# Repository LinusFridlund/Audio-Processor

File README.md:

# Audio-Processor

A modular Raspberry Pi based audio processor with custom designed hardware

## Overview
This audio Processor is a home-stereo DSP unit built around a Raspberry Pi 5. The Pi handles input selection, digital signal processing and the touchscreen UI, while all audio input and output happens on custom PCBs designed from scratch in KiCad.

The hardware is modular, every audio module shares the same 60 × 100 mm, 4-layer form factor and a common 20-pin connector carrying I²S audio, I²C control and power. Modules can be added or swapped without redesigning the rest of the system.

## Hardware

### DAC module
A two-channel, balanced-output DAC using the ESS ES9039Q2M chip. High quality components have been chosen for the best possible performance, including the OPA1612 opamps in the output stages and the ultra low noise power regulators used.

### Digital input module
Receives digital audio from two S/PDIF and tvo coaxial inputs and sends it over I²S to the Raspberry Pi. It is built around the TI SRC4392 IC which handles input multiplexing and sample rate conversion to sync the outgoing data to the Raspberry Pis I²S clock.

### Power Supply
The power supply converts 230V AC from the wall into voltages used by the rest of the system. These include +5V for the Raspberry Pi, and +-15V for the analog boards.

## Software
The software has two main functions, to run a custom GUI made using Kivy in Python, and running the DSP backend. 

## Repository Structure
```
Audio-Processor/
├── Hardware/
│   ├── Digital Input Module/   KiCad project + production files
│   └── DAC Module/             KiCad project, Gerbers, bring-up notes
├── Software/
│   ├── gui/                    Kivy touchscreen interface
│   └── audio_engine/           DSP and hardware control (in progress)
├── docs/                       Diagrams and images
└── LICENSE
```

## Future expansion

## Project Status / Roadmap
Currently the two DAC boards are assembled and initial testing looks promising. An early version of a GUI is up and running on the Raspberry Pi.
My current focus is finishing up the power supply and digital input modules and hopefully getting them ordered soon.

## License
Released under the MIT License.

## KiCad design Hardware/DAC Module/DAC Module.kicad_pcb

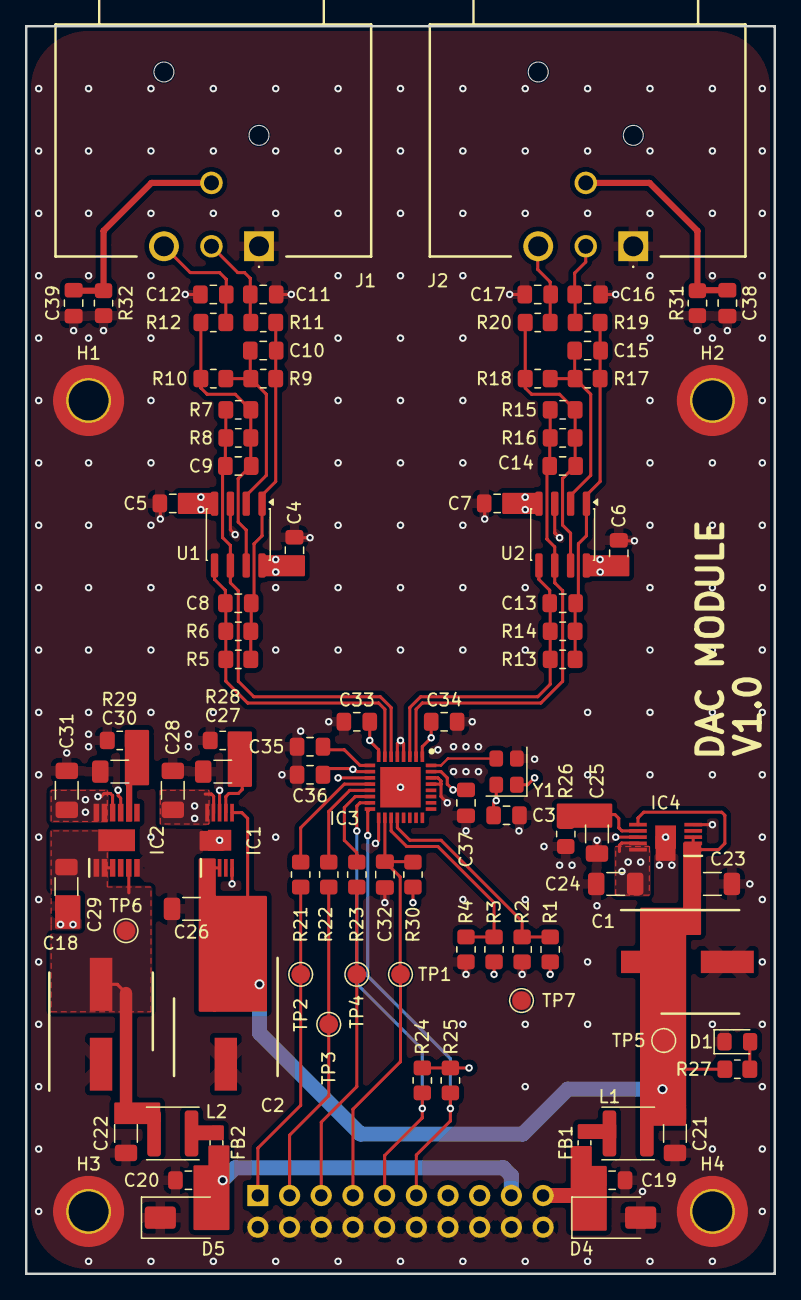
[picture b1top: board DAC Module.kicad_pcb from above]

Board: 4 copper layers, 60.0 x 100.0 mm, 99 parts (1 on the bottom side), 43 nets.

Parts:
C1, C2, C18: 47u; CAPAE830X650N
C3, C19, C20, C32: 100n; C_0805_2012Metric_Pad1.18x1.45mm_HandSolder
C4, C5, C6, C7: 0.47u; C_0805_2012Metric_Pad1.18x1.45mm_HandSolder
C8, C9, C13, C14: 510p (C0G/NP0); C_0805_2012Metric_Pad1.18x1.45mm_HandSolder
C10, C15: 10p (C0G/NP0); C_0805_2012Metric_Pad1.18x1.45mm_HandSolder
C11, C12, C16, C17: 2.2n (C0G/NP0); C_0805_2012Metric_Pad1.18x1.45mm_HandSolder
C21, C22, C24, C28, C31: 10u; C_1206_3216Metric_Pad1.33x1.80mm_HandSolder
C23, C26, C29: 4.7u; C_1206_3216Metric_Pad1.33x1.80mm_HandSolder
C25, C27, C30: 0.47u; C_1206_3216Metric_Pad1.33x1.80mm_HandSolder
C33, C34, C35, C36, C37: 1u; C_0805_2012Metric_Pad1.18x1.45mm_HandSolder
C38, C39: 0.1u; C_0805_2012Metric_Pad1.18x1.45mm_HandSolder
D1: LED; LED_0805_2012Metric_Pad1.15x1.40mm_HandSolder
D4, D5: SMAJ16A; D_SMA
FB1, FB2: BLM18SP601SN1D; L_0603_1608Metric_Pad1.05x0.95mm_HandSolder
H1, H2, H3, H4: M3 hole; MountingHole_3.2mm_M3_ISO7380_Pad_TopBottom
IC1, IC4: LT3042IMSE#PBF; SOP50P490X110-11N
IC2: LT3094IMSE#PBF; SOP65P490X110-13N
IC3: ES9039Q2M; QFN50P500X500X90-33N-D
J1, J2: NC3MAH
J6: Conn_02x10_Odd_Even; PinHeader_2x10_P2.54mm_Vertical
L1, L2: 22uH; L_APV_ANR4026
R1, R2, R3, R4: 0; R_0805_2012Metric_Pad1.20x1.40mm_HandSolder
R5, R6, R7, R8, R13, R14, R15, R16: 3k6 (THIN FILM); R_0805_2012Metric_Pad1.20x1.40mm_HandSolder
R9, R10, R17, R18: 4k7 (THIN FILM); R_0805_2012Metric_Pad1.20x1.40mm_HandSolder
R11, R12, R19, R20: 140 (THIN FILM); R_0805_2012Metric_Pad1.20x1.40mm_HandSolder
R21, R22, R23: 50; R_0805_2012Metric_Pad1.20x1.40mm_HandSolder
R24, R25: 4.7k; R_0805_2012Metric_Pad1.20x1.40mm_HandSolder
R26: 33.2k 1%; R_0805_2012Metric_Pad1.20x1.40mm_HandSolder
R27: 6.8k; R_0805_2012Metric_Pad1.20x1.40mm_HandSolder
R28, R29: 121k 1%; R_0805_2012Metric_Pad1.20x1.40mm_HandSolder
R30: 47k; R_0805_2012Metric_Pad1.20x1.40mm_HandSolder
R31, R32: 10k; R_0805_2012Metric_Pad1.20x1.40mm_HandSolder
TP1, TP2, TP3, TP4, TP5, TP6, TP7: TestPoint_Small; TestPoint_Pad_D1.5mm
U1, U2: OPA1612AxD; SOIC-8_3.9x4.9mm_P1.27mm
Y1: NSC5083D; Oscillator_SMD_Abracon_ASE-4Pin_3.2x2.5mm

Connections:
+3V3: C3.1, C24.1, C33.1, C34.1, C36.1, C37.1, IC3.1 (AVCC_DAC1), IC3.8 (AVCC_DAC2), IC3.10 (AVDD), IC3.31 (VCCA), IC4.9 (OUTS), IC4.10 (OUT), R1.1, R3.1, R24.2, R25.2, R30.2, Y1.1 (EN), Y1.4 (Vdd)
+12V: C4.1, C6.1, C28.1, IC1.9 (OUTS), IC1.10 (OUT), U1.8 (V+), U2.8 (V+)
+15V: C1.1 (+), C2.1 (+), C21.1, C23.1, C26.1, IC1.1 (IN_1), IC1.2 (IN_2), IC1.3 (EN/UV), IC1.6 (PGFB), IC4.1 (IN_1), IC4.2 (IN_2), IC4.3 (EN/UV), IC4.6 (PGFB), L1.2, R27.2, TP5.1 (1_1)
+15V_IN: C19.1, D4.1 (A1), FB1.1, J6.19
-12V: C5.2, C7.2, C31.1, IC2.10 (OUTS), IC2.11 (OUT_1), IC2.12 (OUT_2), U1.4 (V-), U2.4 (V-)
-15V: C18.2 (-), C22.2, C29.1, IC2.1 (IN_1), IC2.2 (IN_2), IC2.3 (EN/UV), IC2.5 (PGFB), IC2.13 (IN_3), L2.2, TP6.1 (1_1)
-15V_IN: C20.2, D5.2 (A2), FB2.1, J6.17
/DAC Module/DVDD: C35.1, IC3.9 (DVDD)
/DAC Module/MCLK: IC3.32 (MCLK), Y1.3 (OUT)
/Power supply/SET_3V3: C25.1, IC4.7 (SET), R26.2
/Power supply/SET_12V: C27.1, IC1.7 (SET), R28.2
/Power supply/SET_-12V: C30.1, IC2.8 (SET), R29.2
ADDR0: IC3.20 (MISO/ADDR0/MUTE_CTRL), R1.2, R2.1
ADDR1: IC3.19 (SS/ADDR1/HW2), R3.2, R4.1
DAC1: C13.1, IC3.3 (DAC1), R13.1, R14.1, U2.5 (+)
DAC1_B: C14.1, IC3.2 (DAC1B), R15.1, R16.1, U2.6 (-)
DAC2: C8.1, IC3.7 (DAC2), R5.1, R6.1, U1.5 (+)
DAC2_B: C9.1, IC3.6 (DAC2B), R7.1, R8.1, U1.6 (-)
DAC_EN: C32.1, IC3.18 (CHIP_EN), J6.7, R30.1, TP1.1 (1_1)
GND: C1.2 (-), C2.2 (-), C3.2, C4.2, C5.1, C6.2, C7.1, C11.1, C12.1, C16.1, C17.1, C18.1 (+), C19.2, C20.1, C21.2, C22.1, C23.2, C24.2, C25.2, C26.2, C27.2, C28.2, C29.2, C30.2, C31.2, C32.2, C33.2, C34.2, C35.2, C36.2, C37.2, C38.1, C39.1, D1.1 (K), D4.2 (A2), D5.1 (A1), H1.1 (1_1), H2.1 (1_1), H3.1 (1_1), H4.1 (1_1), IC1.5 (ILIM), IC1.8 (GND_1), IC1.11 (GND_2), IC2.6 (I_LIM), IC2.9 (GND), IC3.4 (AGND_DAC1), IC3.5 (AGND_DAC2), IC3.11 (GND_1), IC3.17 (RT1), IC3.29 (MODE), IC3.30 (GND_2), IC3.33 (GND_3), IC4.5 (ILIM), IC4.8 (GND_1), IC4.11 (GND_2), J1.1, J2.1, J6.2, J6.4, J6.6, J6.8, J6.10, J6.12, J6.14, J6.16, J6.18, J6.20, R2.2, R4.2, R26.1, R28.1, R29.1, R31.1, R32.1, TP7.1 (1_1), U1.3 (+), U2.3 (+), Y1.2 (GND)
I2C_SCL: IC3.15 (SCLK/SCL/HW1), J6.9, R24.1
I2C_SDA: IC3.16 (MOSI/SDA/HW0), J6.11, R25.1
I2S_BCLK: J6.1, R21.1, TP2.1 (1_1)
I2S_DATA: J6.5, R23.1, TP4.1 (1_1)
I2S_WCLK: J6.3, R22.1, TP3.1 (1_1)
unnamed: C9.2, R7.2, R8.2, R10.2, R12.1, U1.7
unnamed: C8.2, C10.2, R5.2, R6.2, R9.1, R11.1, U1.1
unnamed: C11.2, J1.3, R11.2
unnamed: C12.2, J1.2, R12.2
unnamed: C13.2, C15.2, R13.2, R14.2, R17.1, R19.1, U2.1
unnamed: C14.2, R15.2, R16.2, R18.2, R20.1, U2.7
unnamed: C16.2, J2.3, R19.2
unnamed: C17.2, J2.2, R20.2
unnamed: C38.2, J2.G1, R31.2
unnamed: C39.2, J1.G1, R32.2
unnamed: D1.2 (A), R27.1
unnamed: FB1.2, L1.1
unnamed: FB2.2, L2.1
unnamed: IC3.13 (DATA1), R22.2
unnamed: IC3.14 (DATA2), R23.2
unnamed: IC3.12 (DATA_CLK), R21.2
unnamed: C10.1, R9.2, R10.1, U1.2 (-)
unnamed: C15.1, R17.2, R18.1, U2.2 (-)

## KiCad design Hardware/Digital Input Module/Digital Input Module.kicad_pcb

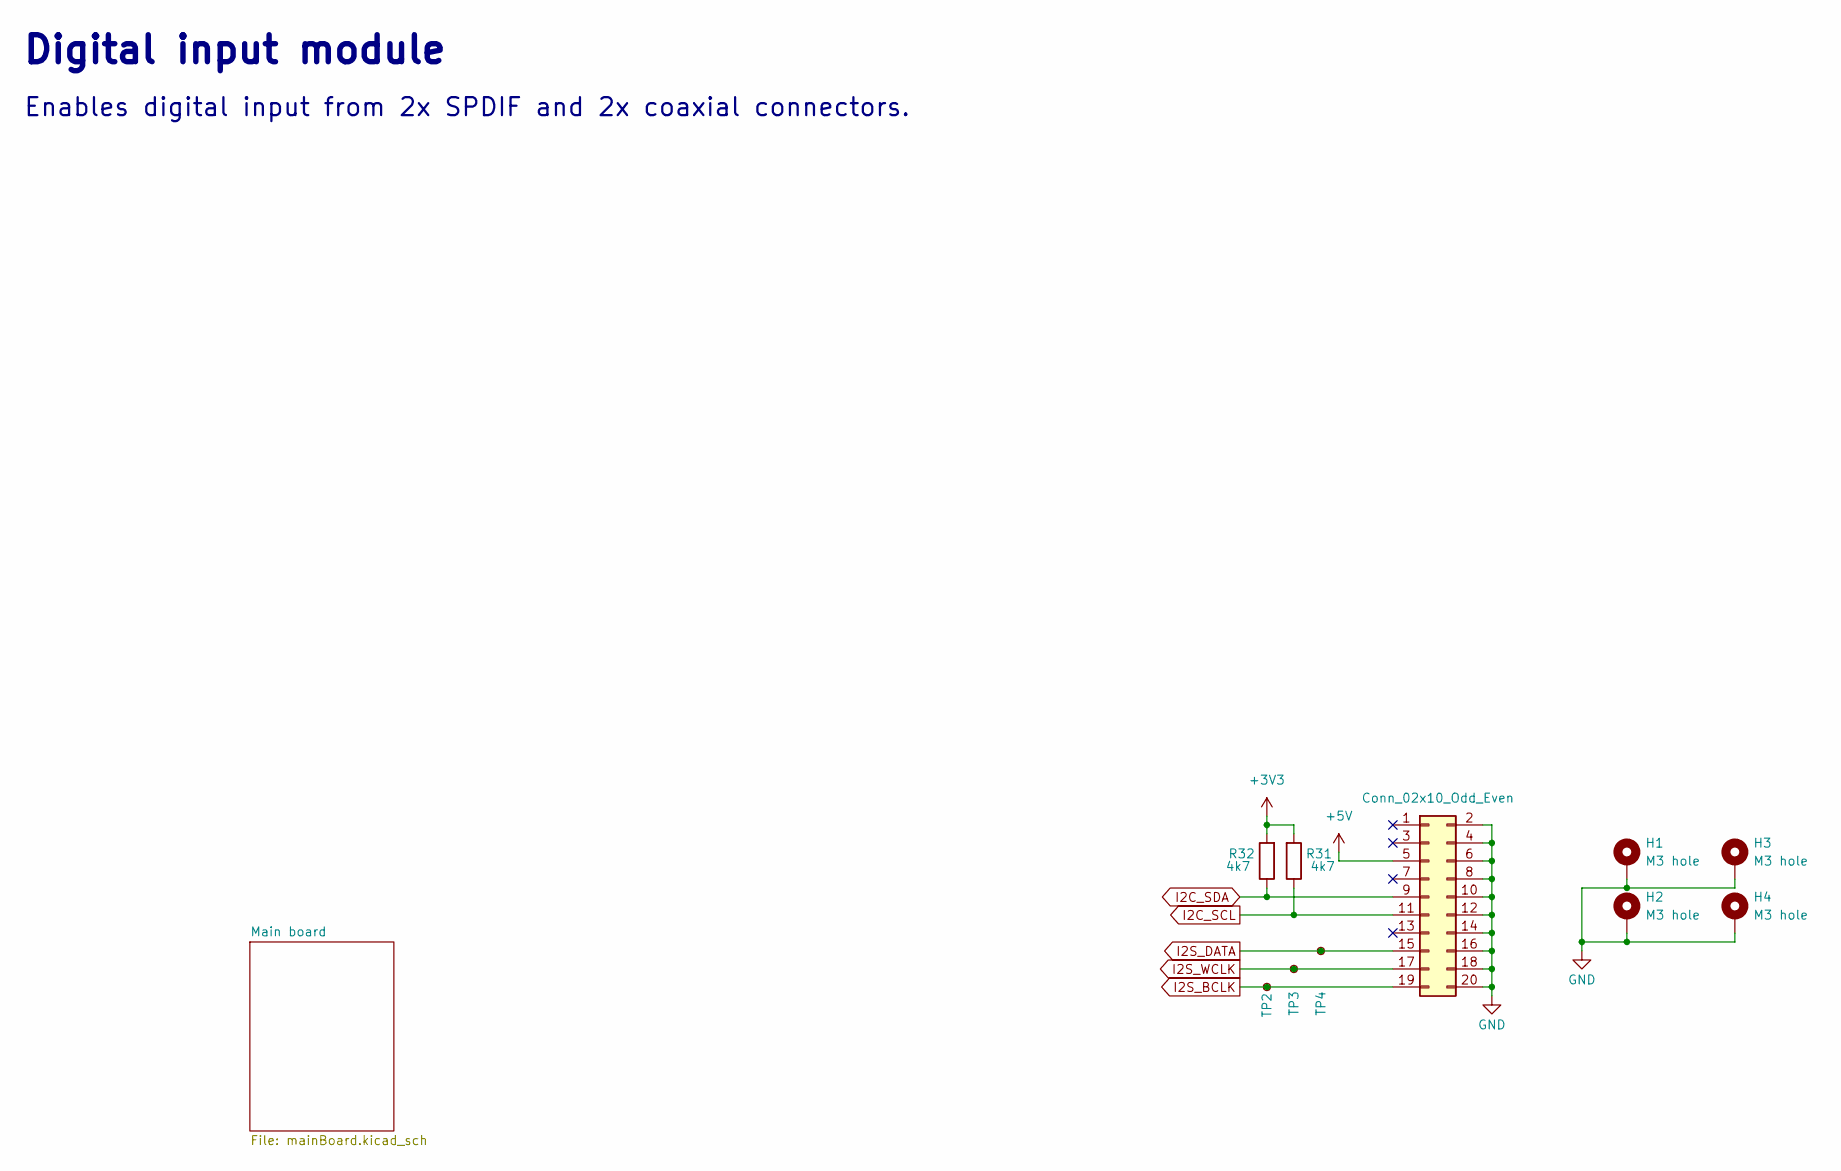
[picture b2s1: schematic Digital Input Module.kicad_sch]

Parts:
H1, H2, H3, H4: M3 hole; MountingHole_3.2mm_M3_ISO7380_Pad_TopBottom
J2: Conn_02x10_Odd_Even; PinHeader_2x10_P2.54mm_Vertical
R31, R32: 4k7; R_0805_2012Metric_Pad1.20x1.40mm_HandSolder
TP2, TP3, TP4: TestPoint_Small; TestPoint_Pad_D1.5mm

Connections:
+3V3: R31.2, R32.2; also elsewhere on the board
+5V: J2.5; also elsewhere on the board
GND: H1.1 (1_1), H2.1 (1_1), H3.1 (1_1), H4.1 (1_1), J2.2, J2.4, J2.6, J2.8, J2.10, J2.12, J2.14, J2.16, J2.18, J2.20; also elsewhere on the board
I2C_SCL: J2.11, R31.1; also elsewhere on the board
I2C_SDA: J2.9, R32.1; also elsewhere on the board
I2S_BCLK: J2.19, TP2.1; also elsewhere on the board
I2S_DATA: J2.15, TP4.1; also elsewhere on the board
I2S_WCLK: J2.17, TP3.1; also elsewhere on the board

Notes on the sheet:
Digital input module
Enables digital input from 2x SPDIF and 2x coaxial connectors.

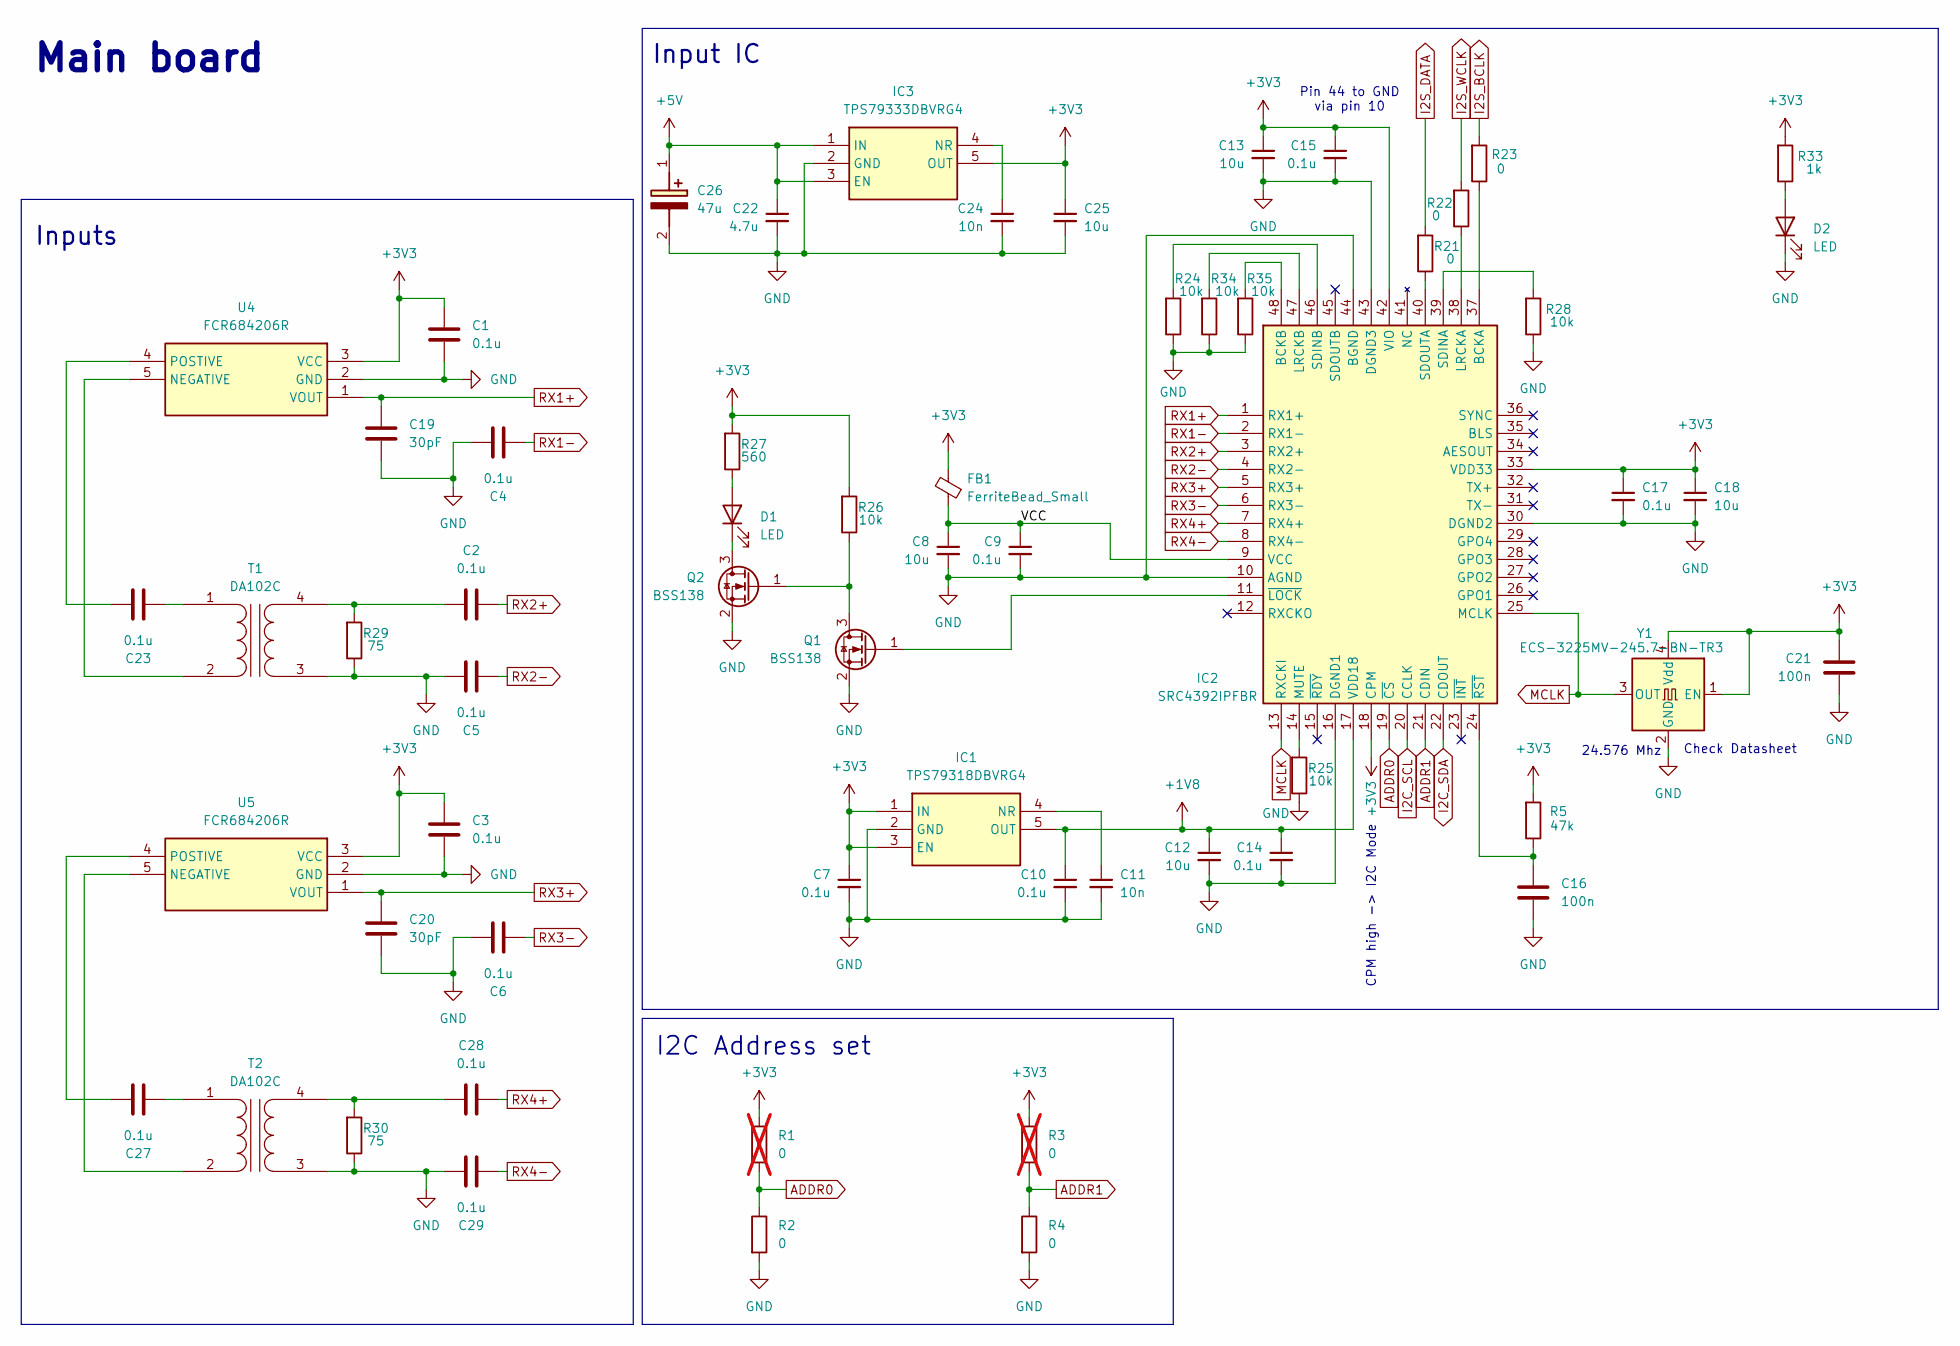
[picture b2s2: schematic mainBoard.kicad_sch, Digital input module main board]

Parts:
C1, C2, C3, C4, C5, C6, C7, C9, C10, C14, C15, C17, C23, C27, C28, C29: 0.1u; C_0805_2012Metric_Pad1.18x1.45mm_HandSolder
C8, C12, C13, C18, C25: 10u; C_0805_2012Metric_Pad1.18x1.45mm_HandSolder
C11, C24: 10n; C_0805_2012Metric_Pad1.18x1.45mm_HandSolder
C16, C21: 100n; C_0805_2012Metric_Pad1.18x1.45mm_HandSolder
C19, C20: 30pF; C_0805_2012Metric_Pad1.18x1.45mm_HandSolder
C22: 4.7u; C_0805_2012Metric_Pad1.18x1.45mm_HandSolder
C26: 47u; CAPAE830X650N; Manufacturer_Part_Number 865080649013; Mouser Part Number 710-865080649013
D1, D2: LED; LED_0805_2012Metric_Pad1.15x1.40mm_HandSolder
FB1: FerriteBead_Small; L_0603_1608Metric_Pad1.05x0.95mm_HandSolder
IC1: TPS79318DBVRG4; SOT95P280X145-5N; Manufacturer_Part_Number TPS79318DBVRG4; Mouser Part Number 595-TPS79318DBVRG4
IC2: SRC4392IPFBR; QFP50P900X900X120-48N; Manufacturer_Part_Number SRC4392IPFBR; Mouser Part Number 595-SRC4392IPFBR
IC3: TPS79333DBVRG4; SOT95P280X145-5N; Manufacturer_Part_Number TPS79318DBVRG4; Mouser Part Number 595-TPS79318DBVRG4
Q1, Q2: BSS138; SOT-23
R1, R3: 0; R_0805_2012Metric_Pad1.20x1.40mm_HandSolder; not fitted
R2, R4, R21, R22, R23: 0; R_0805_2012Metric_Pad1.20x1.40mm_HandSolder
R5: 47k; R_0805_2012Metric_Pad1.20x1.40mm_HandSolder
R24, R25, R26, R28, R34, R35: 10k; R_0805_2012Metric_Pad1.20x1.40mm_HandSolder
R27: 560; R_0805_2012Metric_Pad1.20x1.40mm_HandSolder
R29, R30: 75; R_0805_2012Metric_Pad1.20x1.40mm_HandSolder
R33: 1k; R_0805_2012Metric_Pad1.20x1.40mm_HandSolder
T1, T2: DA102C
U4, U5: FCR684206R; Manufacturer_Part_Number FCR684206R
Y1: ECS-3225MV-245.7-BN-TR3; Oscillator_SMD_Abracon_ASE-4Pin_3.2x2.5mm

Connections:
+1V8: C10.1, C12.1, C14.1, IC1.5 (OUT), IC2.17 (VDD18)
+3V3: C1.2, C3.2, C7.1, C13.1, C15.1, C17.1, C18.1, C21.1, C25.1, FB1.2, IC1.1 (IN), IC1.3 (EN), IC2.18 (CPM), IC2.33 (VDD33), IC2.42 (VIO), IC3.5 (OUT), R1.1, R3.1, R5.2, R26.2, R27.2, R33.2, U4.3 (VCC), U5.3 (VCC), Y1.1 (EN), Y1.4 (Vdd); also elsewhere on the board
+5V: C22.1, C26.1 (+), IC3.1 (IN), IC3.3 (EN); also elsewhere on the board
/Main board/VCC: C8.1, C9.1, FB1.1, IC2.9 (VCC)
ADDR0: IC2.19 (~CS), R1.2, R2.1
ADDR1: IC2.21 (CDIN), R3.2, R4.1
GND: C1.1, C3.1, C4.2, C5.2, C6.2, C7.2, C8.2, C9.2, C10.2, C11.2, C12.2, C13.2, C14.2, C15.2, C16.2, C17.2, C18.2, C19.1, C20.1, C21.2, C22.2, C24.2, C25.2, C26.2 (-), C29.2, D2.1 (K), IC1.2 (GND), IC2.10 (AGND), IC2.16 (DGND1), IC2.30 (DGND2), IC2.43 (DGND3), IC2.44 (BGND), IC3.2 (GND), Q1.2 (S), Q2.2 (S), R2.2, R4.2, R24.1, R25.1, R28.1, R29.1, R30.1, R34.1, R35.1, T1.3 (SA), T2.3 (SA), U4.2 (GND), U5.2 (GND), Y1.2 (GND); also elsewhere on the board
I2C_SCL: IC2.20 (CCLK); also elsewhere on the board
I2C_SDA: IC2.22 (CDOUT); also elsewhere on the board
I2S_BCLK: R23.2; also elsewhere on the board
I2S_DATA: R21.2; also elsewhere on the board
I2S_WCLK: R22.2; also elsewhere on the board
MCLK: IC2.13 (RXCKI), IC2.25 (MCLK), Y1.3 (OUT)
unnamed: D1.2 (A), R27.1
unnamed: D1.1 (K), Q2.3 (D)
unnamed: D2.2 (A), R33.1
unnamed: C11.1, IC1.4 (NR)
unnamed: IC2.37 (BCKA), R23.1
unnamed: IC2.48 (BCKB), R35.2
unnamed: IC2.38 (LRCKA), R22.1
unnamed: IC2.47 (LRCKB), R34.2
unnamed: IC2.14 (MUTE), R25.2
unnamed: IC2.39 (SDINA), R28.2
unnamed: IC2.46 (SDINB), R24.2
unnamed: IC2.40 (SDOUTA), R21.1
unnamed: IC2.11 (~LOCK), Q1.1 (G)
unnamed: C16.1, IC2.24 (~RST), R5.1
unnamed: C24.1, IC3.4 (NR)
unnamed: Q1.3 (D), Q2.1 (G), R26.1
unnamed: C23.1, T1.1 (AA)
unnamed: T1.2 (AB), U4.5 (NEGATIVE)
unnamed: C2.2, R29.2, T1.4 (SB)
unnamed: C27.1, T2.1 (AA)
unnamed: T2.2 (AB), U5.5 (NEGATIVE)
unnamed: C28.2, R30.2, T2.4 (SB)
unnamed: C23.2, U4.4 (POSTIVE)
unnamed: C27.2, U5.4 (POSTIVE)
RX1+: C19.2, IC2.1 (RX1+), U4.1 (VOUT)
RX1-: C4.1, IC2.2 (RX1-)
RX2+: C2.1, IC2.3 (RX2+)
RX2-: C5.1, IC2.4 (RX2-)
RX3+: C20.2, IC2.5 (RX3+), U5.1 (VOUT)
RX3-: C6.1, IC2.6 (RX3-)
RX4+: C28.1, IC2.7 (RX4+)
RX4-: C29.1, IC2.8 (RX4-)

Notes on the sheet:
Input IC
Main board
Pin 44 to GND via pin 10
I2C Address set
CPM high -> I2C Mode
Check Datasheet
24.576 Mhz
Inputs

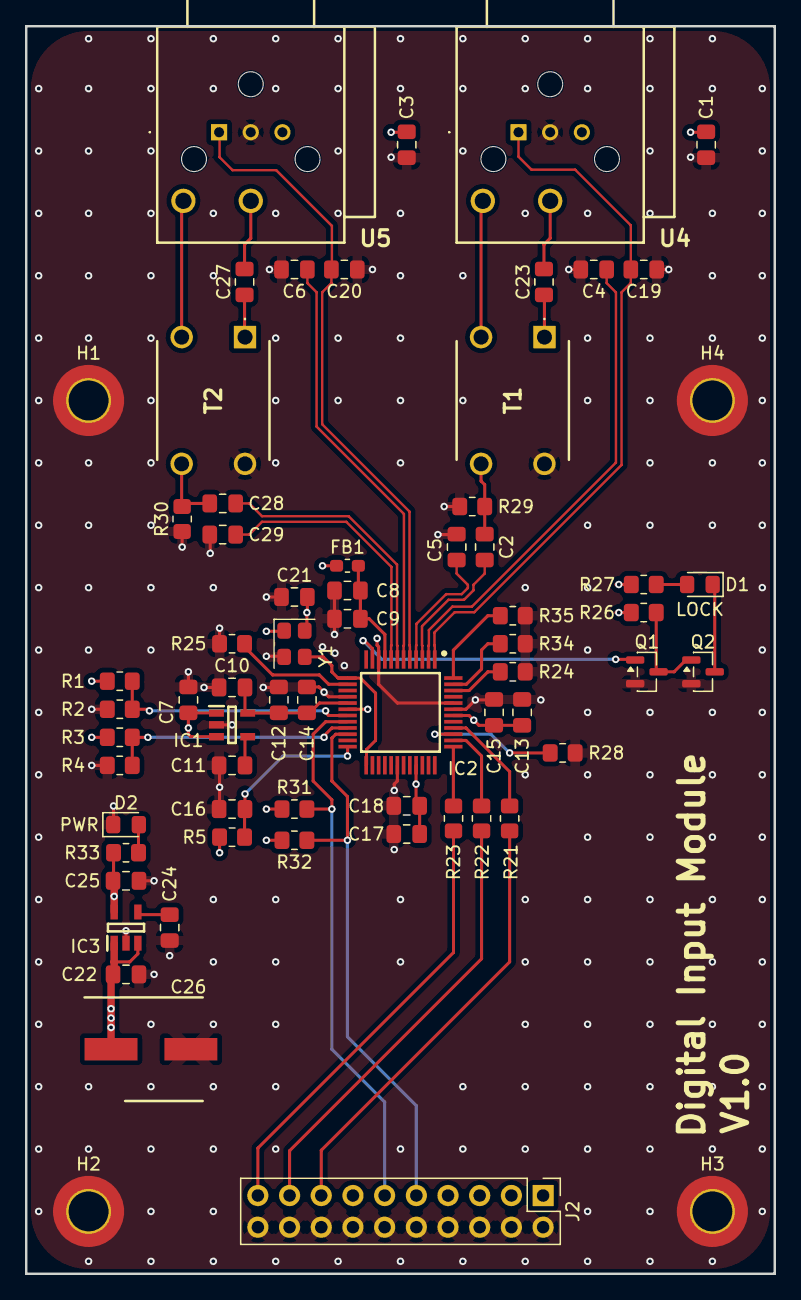
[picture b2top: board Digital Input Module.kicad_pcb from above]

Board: 4 copper layers, 60.0 x 100.0 mm, 67 parts (0 on the bottom side), 45 nets.

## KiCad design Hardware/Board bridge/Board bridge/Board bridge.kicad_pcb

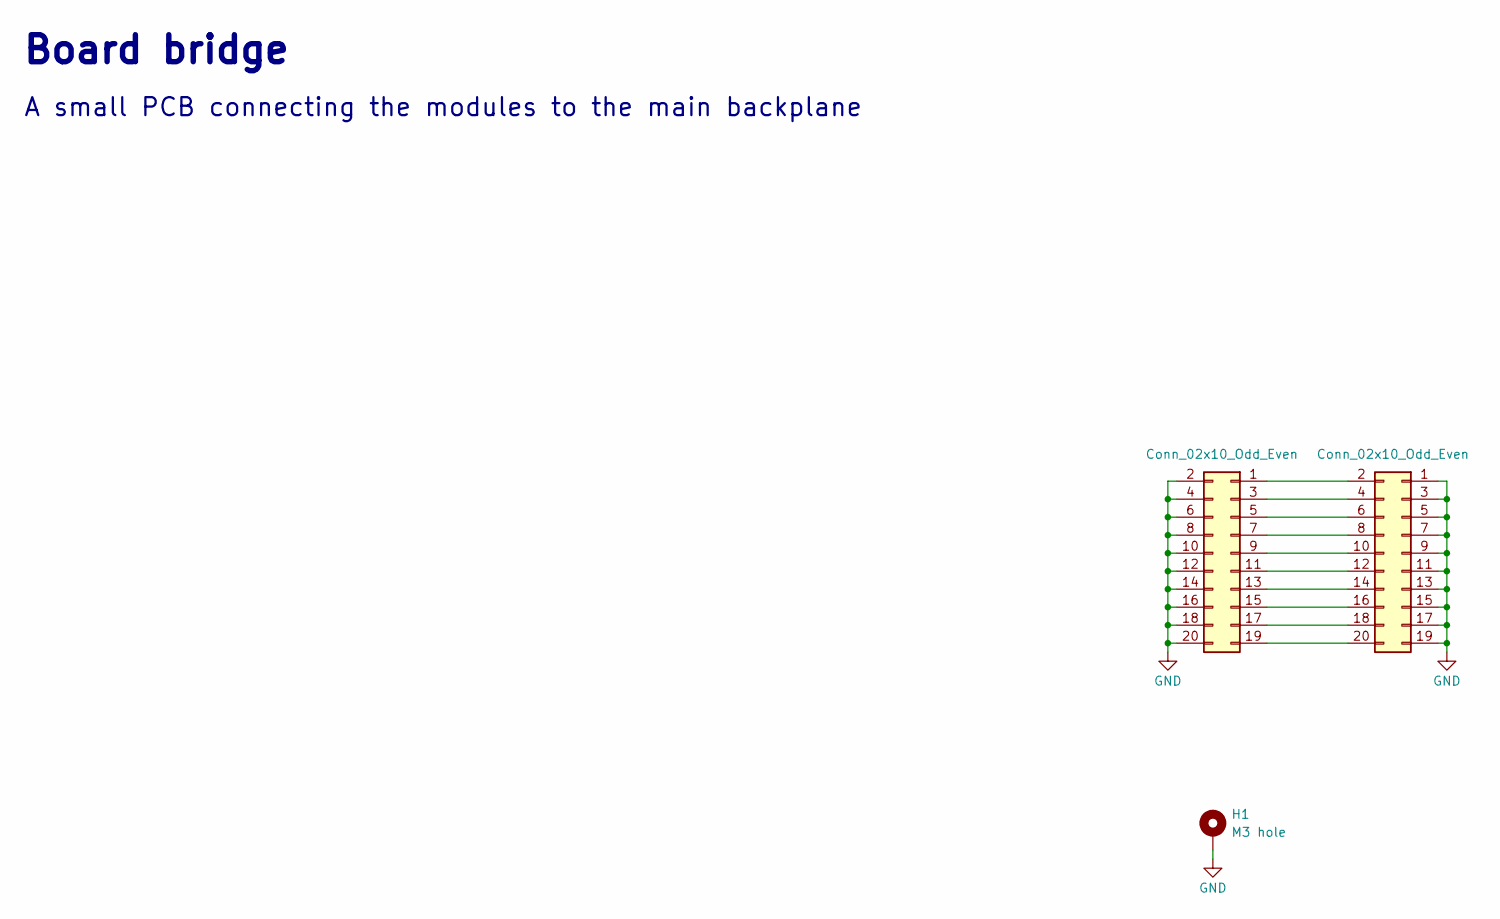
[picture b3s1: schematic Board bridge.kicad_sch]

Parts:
H1: M3 hole; MountingHole_3.2mm_M3_ISO7380_Pad_TopBottom
J2, J3: Conn_02x10_Odd_Even; PinSocket_2x10_P2.54mm_Vertical

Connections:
GND: H1.1 (1_1), J2.2, J2.4, J2.6, J2.8, J2.10, J2.12, J2.14, J2.16, J2.18, J2.20, J3.1, J3.3, J3.5, J3.7, J3.9, J3.11, J3.13, J3.15, J3.17, J3.19
unnamed: J2.1, J3.2
unnamed: J2.3, J3.4
unnamed: J2.5, J3.6
unnamed: J2.7, J3.8
unnamed: J2.9, J3.10
unnamed: J2.11, J3.12
unnamed: J2.13, J3.14
unnamed: J2.15, J3.16
unnamed: J2.17, J3.18
unnamed: J2.19, J3.20

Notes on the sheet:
A small PCB connecting the modules to the main backplane
Board bridge

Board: 2 copper layers, 3 parts (2 on the bottom side), 11 nets, no tracks yet.
